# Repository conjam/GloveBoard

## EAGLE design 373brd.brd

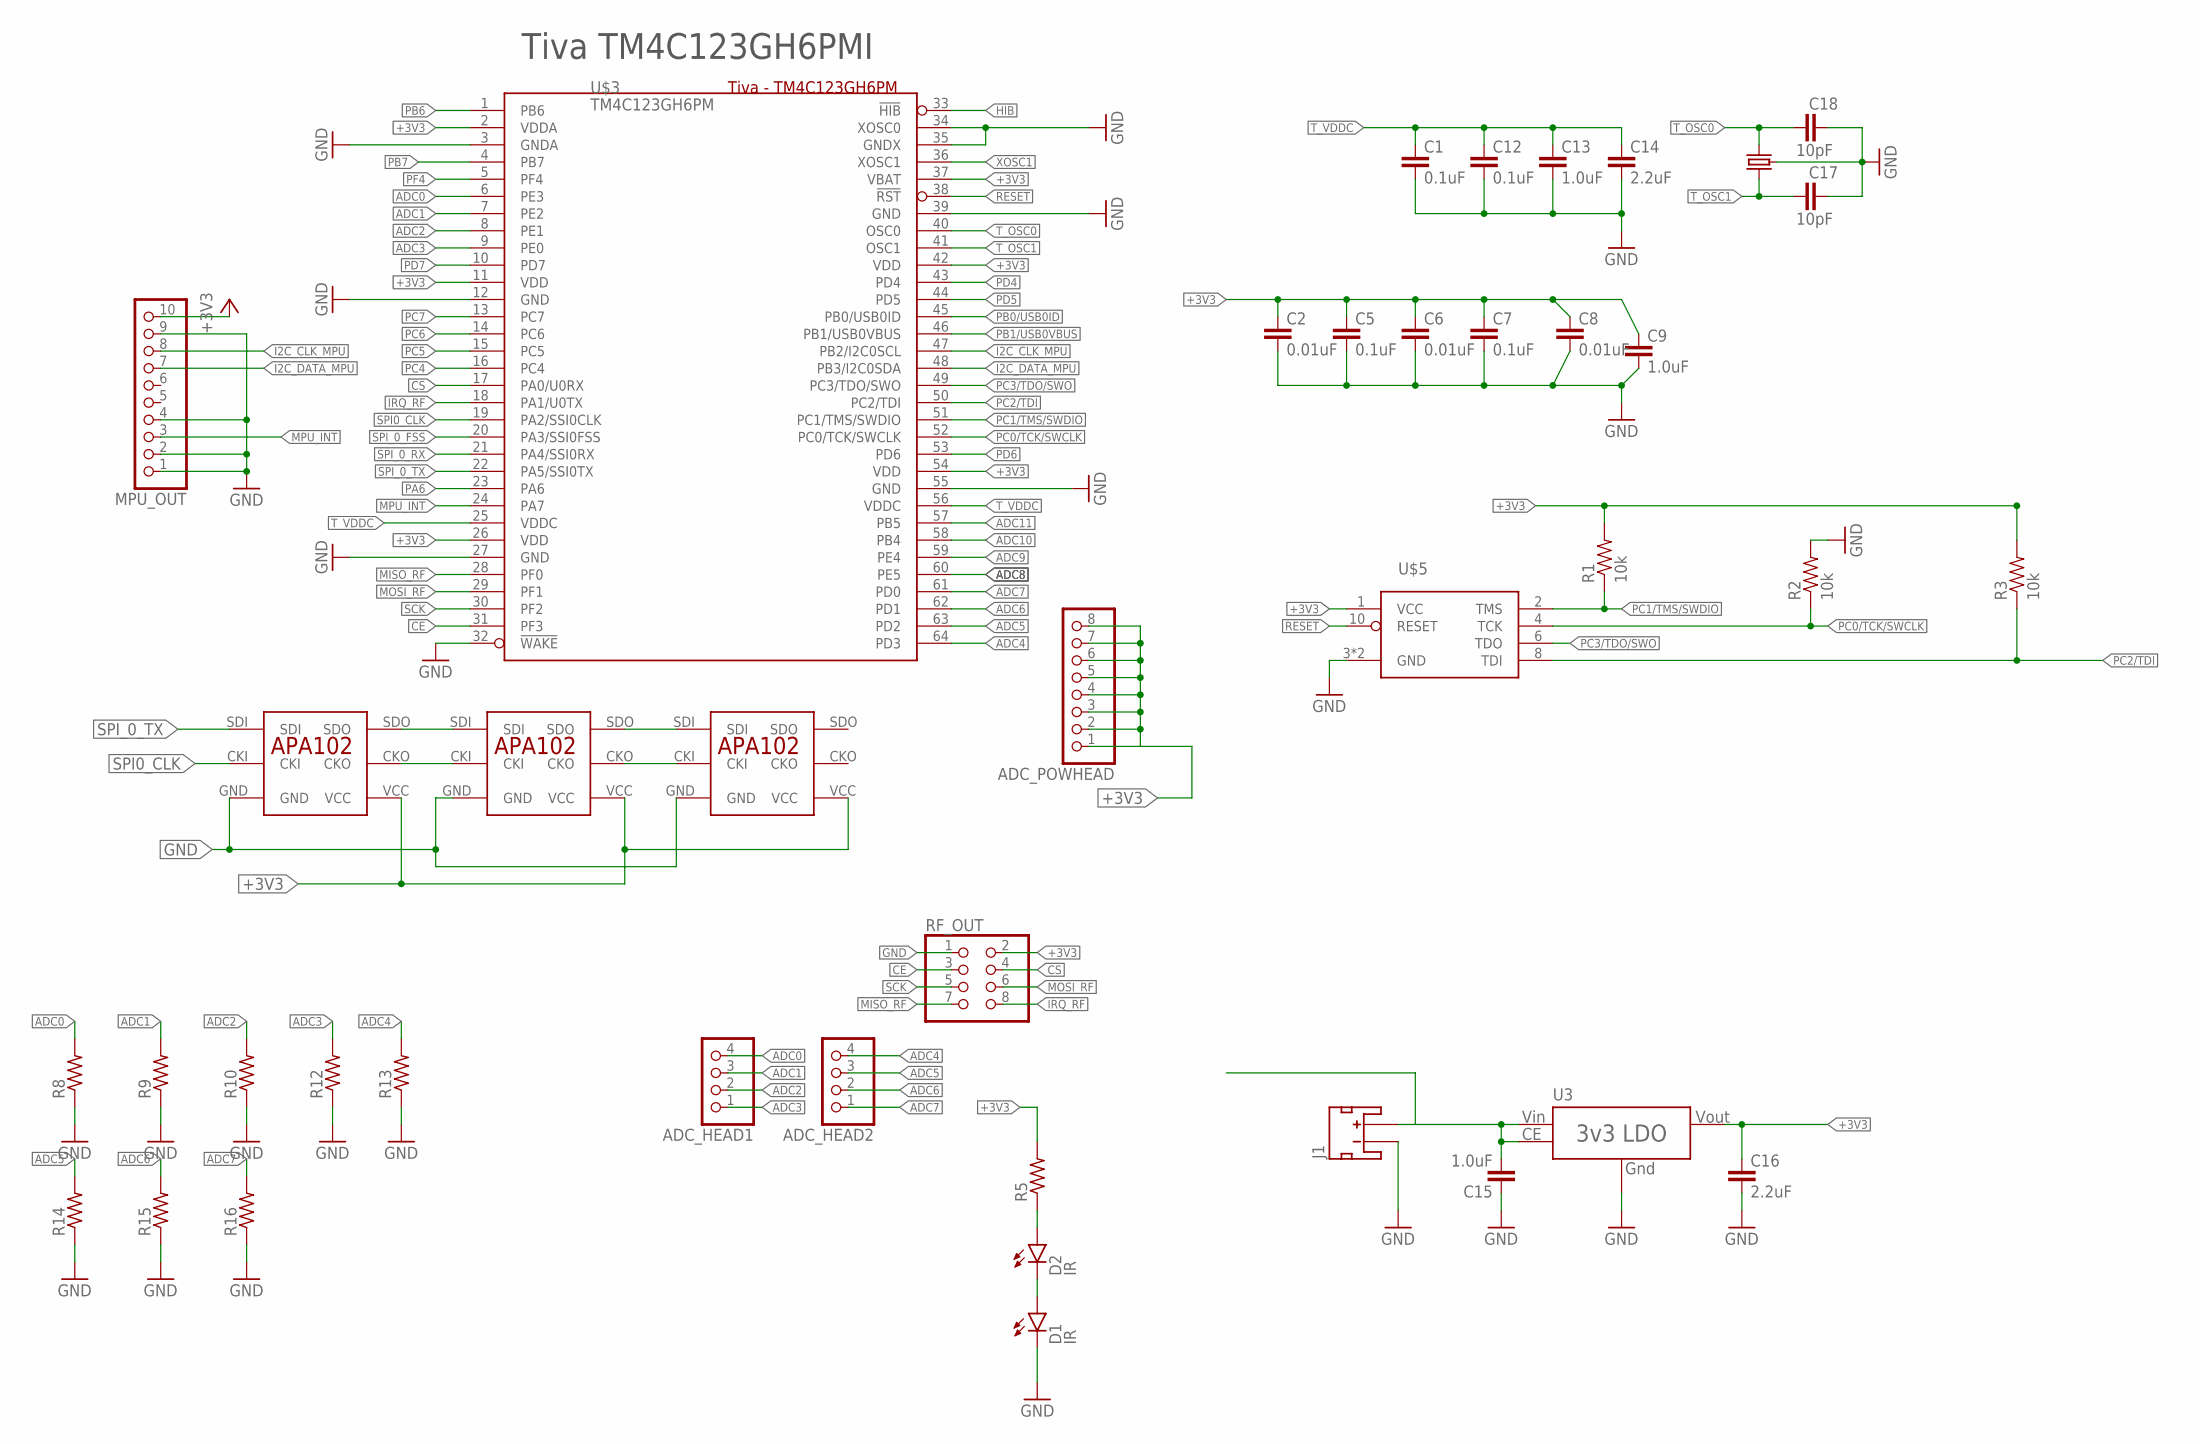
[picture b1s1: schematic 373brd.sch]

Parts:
ADC_HEAD1, ADC_HEAD2: PINHD-1X4; 1X04
ADC_POWHEAD: PINHD-1X8; 1X08
C1, C5, C7, C12: 0.1uF; C0603
C2, C6, C8: 0.01uF; C0603
C9, C13: 1.0uF; C0603
C14: 2.2uF; C0603
C15: 1.0uF; C0805
C16: 2.2uF; C0805
C17, C18: 10pF; C0603; DIGIKEY# 399-1049-1-ND
D1, D2: IR; LED-1206
J1: JST_2MM_MALE; JST-2-SMD
MPU_OUT: PINHD-1X10; 1X10
R1, R2, R3: 10k; 0603-RES
R5, R8, R9, R10, R12, R13, R14, R15, R16: R-US_R0603; R0603
RF_OUT: PINHD-2X4; 2X04
U3: XC6210; SOT-25
U$1: CRYSTAL_403C11E16; 4-SMD-SWITCH
U$2, U$4, U$6: APA102
U$3: TM4C123GH6PM; DIGIKEY# 296-35849-ND
U$5: JTAG-ARM_TC-10; TC2050-IDC

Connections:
+3V3: ADC_POWHEAD.1, ADC_POWHEAD.2, ADC_POWHEAD.3, ADC_POWHEAD.4, ADC_POWHEAD.5, ADC_POWHEAD.6, ADC_POWHEAD.7, ADC_POWHEAD.8, C2.1, C5.1, C6.1, C7.1, C8.1, C9.1, C16.1, MPU_OUT.10, R1.2, R3.2, R5.2, RF_OUT.2, U3.5 (VOUT), U$2.VCC, U$3.2 (VDDA), U$3.11 (VDD), U$3.26 (VDD), U$3.37 (VBAT), U$3.42 (VDD), U$3.54 (VDD), U$4.VCC, U$5.1 (VCC), U$6.VCC
ADC0: ADC_HEAD1.4, R8.2, U$3.6 (PE3)
ADC1: ADC_HEAD1.3, R9.2, U$3.7 (PE2)
ADC2: ADC_HEAD1.2, R10.2, U$3.8 (PE1)
ADC3: ADC_HEAD1.1, R12.2, U$3.9 (PE0)
ADC4: ADC_HEAD2.4, R13.2, U$3.64 (PD3)
ADC5: ADC_HEAD2.3, R14.2, U$3.63 (PD2)
ADC6: ADC_HEAD2.2, R15.2, U$3.62 (PD1)
ADC7: ADC_HEAD2.1, R16.2, U$3.61 (PD0)
ADC8: U$3.60 (PE5)
ADC9: U$3.59 (PE4)
ADC10: U$3.58 (PB4)
ADC11: U$3.57 (PB5)
BATT_IN: C15.2, J1.2 (+), U3.1 (VIN), U3.3 (CE)
CE: RF_OUT.3, U$3.31 (PF3)
CS: RF_OUT.4, U$3.17 (PA0/U0RX)
GND: C1.2, C2.2, C5.2, C6.2, C7.2, C8.2, C9.2, C12.2, C13.2, C14.2, C15.1, C16.2, C17.2, C18.2, D1.C, J1.1 (-), MPU_OUT.1, MPU_OUT.2, MPU_OUT.4, MPU_OUT.9, R2.2, R8.1, R9.1, R10.1, R12.1, R13.1, R14.1, R15.1, R16.1, RF_OUT.1, U3.2 (GND), U$1.2 (GND), U$1.4 (GND), U$2.GND, U$3.3 (GNDA), U$3.12 (GND), U$3.27 (GND), U$3.32 (!WAKE), U$3.34 (XOSC0), U$3.35 (GNDX), U$3.39 (GND), U$3.55 (GND), U$4.GND, U$5.3 (GND), U$5.9 (GND), U$6.GND
HIB: U$3.33 (!HIB)
I2C_CLK_MPU: MPU_OUT.8, U$3.47 (PB2/I2C0SCL)
I2C_DATA_MPU: MPU_OUT.7, U$3.48 (PB3/I2C0SDA)
IRQ_RF: RF_OUT.8, U$3.18 (PA1/U0TX)
MISO_RF: RF_OUT.7, U$3.28 (PF0)
MOSI_RF: RF_OUT.6, U$3.29 (PF1)
MPU_INT: MPU_OUT.3, U$3.24 (PA7)
unnamed: U$2.SDO, U$4.SDI
unnamed: U$2.CKO, U$4.CKI
unnamed: U$4.SDO, U$6.SDI
unnamed: U$4.CKO, U$6.CKI
unnamed: D1.A, D2.C
unnamed: D2.A, R5.1
PA6: U$3.23 (PA6)
PB0/USB0ID: U$3.45 (PB0/USB0ID)
PB1/USB0VBUS: U$3.46 (PB1/USB0VBUS)
PB6: U$3.1 (PB6)
PB7: U$3.4 (PB7)
PC0/TCK/SWCLK: R2.1, U$3.52 (PC0/TCK/SWCLK), U$5.4 (TCK)
PC1/TMS/SWDIO: R1.1, U$3.51 (PC1/TMS/SWDIO), U$5.2 (TMS)
PC2/TDI: R3.1, U$3.50 (PC2/TDI), U$5.8 (TDI)
PC3/TDO/SWO: U$3.49 (PC3/TDO/SWO), U$5.6 (TDO)
PC4: U$3.16 (PC4)
PC5: U$3.15 (PC5)
PC6: U$3.14 (PC6)
PC7: U$3.13 (PC7)
PD4: U$3.43 (PD4)
PD5: U$3.44 (PD5)
PD6: U$3.53 (PD6)
PD7: U$3.10 (PD7)
PF4: U$3.5 (PF4)
RESET: U$3.38 (!RST), U$5.10 (RESET)
SCK: RF_OUT.5, U$3.30 (PF2)
SPI0_CLK: U$2.CKI, U$3.19 (PA2/SSI0CLK)
SPI_0_FSS: U$3.20 (PA3/SSI0FSS)
SPI_0_RX: U$3.21 (PA4/SSI0RX)
SPI_0_TX: U$2.SDI, U$3.22 (PA5/SSI0TX)
T_OSC0: C18.1, U$1.3 (2), U$3.40 (OSC0)
T_OSC1: C17.1, U$1.1, U$3.41 (OSC1)
T_VDDC: C1.1, C12.1, C13.1, C14.1, U$3.25 (VDDC), U$3.56 (VDDC)
XOSC1: U$3.36 (XOSC1)

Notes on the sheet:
Tiva TM4C123GH6PMI

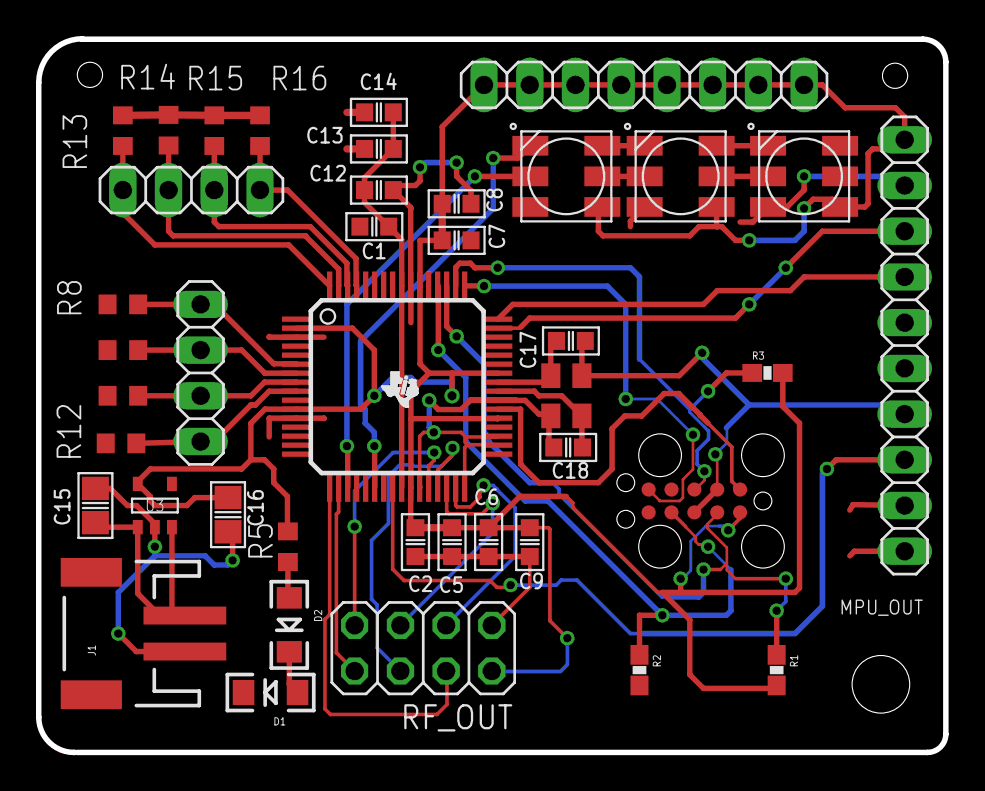
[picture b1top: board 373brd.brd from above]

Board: 2 copper layers, 50.4 x 39.6 mm, 41 parts (0 on the bottom side), 36 nets.

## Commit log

2016-03-07 Circuit done, just routing
2016-03-07 my gitignore dun goofed
2016-03-12 finished routing
2016-03-14 done for real
2016-03-20 Gerber's zipped up
2016-03-20 general arch for glove
2016-03-21 new brd
2016-03-21 rename
2016-03-23 nrf_done??
2016-03-23 tiva test
2016-03-23 for smartfusion
2016-04-02 added ADC files

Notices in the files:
parts and their libraries:
SparkFun-Resistors: Licensing: CC v3.0 Share-Alike You are welcome to use this library for commercial purposes.
SparkFun-LED: Licensing: Creative Commons ShareAlike 4.0 International - https://creativecommons.org/licenses/by-sa/4.0
